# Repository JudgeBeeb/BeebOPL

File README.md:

# BeebOPL
## An FM synthesiser for the BBC Microcomputer based on the YM3812

This is an FM Synthesiser Sound Card for the BBC Microcomputer. It is based on the YM3812 chip as used in the Ad Lib Sound Card and the original Soundblaster. 

It connects to the 1MHz Bus and is programmed by reference to two addresses in the BBC memory map. These are `YMADDR` (&FC04) and `YMDATA` (&FC04).

For some samples of what BeebOPL can do have a look at this [playlist on SoundCloud] (https://soundcloud.com/user-469563483/sets/beebopl-1)

The `DROPLAY` utility will play _DOSBox Raw OPL_ (DRO) version 2.0 files natively. These files can be generated by playing any OPL file in DOSBox (version 0.74). Visit http://www.dosbox.com for details.

The syntax for the compiled executable is `*DROPLAY <fsp>`. The code is compiled to load in the page above `PAGE`. It loads as much as it can of the DRO file from the page immediately above the program up to the page below `HIMEM`. If the entire file fits into memory, it is simply played from memory. Otherwise, further data is streamed from the disc using `OSGBPB` in the form of a circular buffer. 

All disc reads take place in the foreground. The music player itself is an interrupt driven background task. Interrupts are generated by the YM3812 timer. This avoids using the User VIA timer as this seems to interfere with certain solid state filing system.

**_Issues and to do_**

- [x] ~~System crashes following use of the `ESCAPE` key.~~

- [x] ~~Check for the presence of a BeebOPL card before attempting to play a file and issue error.~~

- [x] ~~Include error messages for card not found, not a valid DRO file, unsupported DRO version, wrong card version and compressed file not supported.~~ 

- [ ] The YM3812 flush routine doesn't seem to work all the time. Subsequent tunes can be a little corrupted if they are played without a preceding hard break.

- [ ] Due to an inherent problem with OSGBPB, the filing system cannot keep up with the demands of particularly large/complex DRO files. The player effectively '_laps_' the circular buffer and starts repeating the same segment of the file.

- [x] ~~Check if the entire DRO file will fit in memory and, if so, load it with `OSFILE` rather than `OSGBPB` to speed up loading times.~~

- [ ] Address continuing minor timing issues. (These seem to be getting worse!) ~~DRO timing data is based on milliseconds. The YM3812 timer updates every 80 microseconds and therefore cannot measure precisely one millisecond.~~ 

- [x] ~~Check to see if player has overtaken buffer and issue error.~~

- [x] ~~Find a neat way to deal with buffering messages in Juke Box.~~

- [x] ~~The registers are flushed too soon. Need to leave time for the last note to fade.~~

- [x] ~~Generally tidy up code; in particular using curly braces and local variables.~~

- [x] ~~Juke Box inexplicably occasionally reports "BeebOPL card not found".~~

- [x] ~~The 3.5mm jack socket is about 1mm too far over to the left and therefore does not fit well. This needs to be corrected if another run of boards is done.~~

- [] There is an error on the PCB silk screen at the 'floppy' style power connector. 5v and 12v are reversed.

Further down the line, I would like to see if the use of [Exomiser] (http://hem.bredband.net/magli143/exo/) could be incorporated.

I would also like to see if I could include **kieranhj**'s direct track loading routines using `OSWORD` (which he uses in his amazing [Mode 7 Video] (https://github.com/kieranhj/mode7-video) project). This may resolves the problems associated with `OSGBPB`.

It would also be useful if there could be some kind of (software) master volume control.

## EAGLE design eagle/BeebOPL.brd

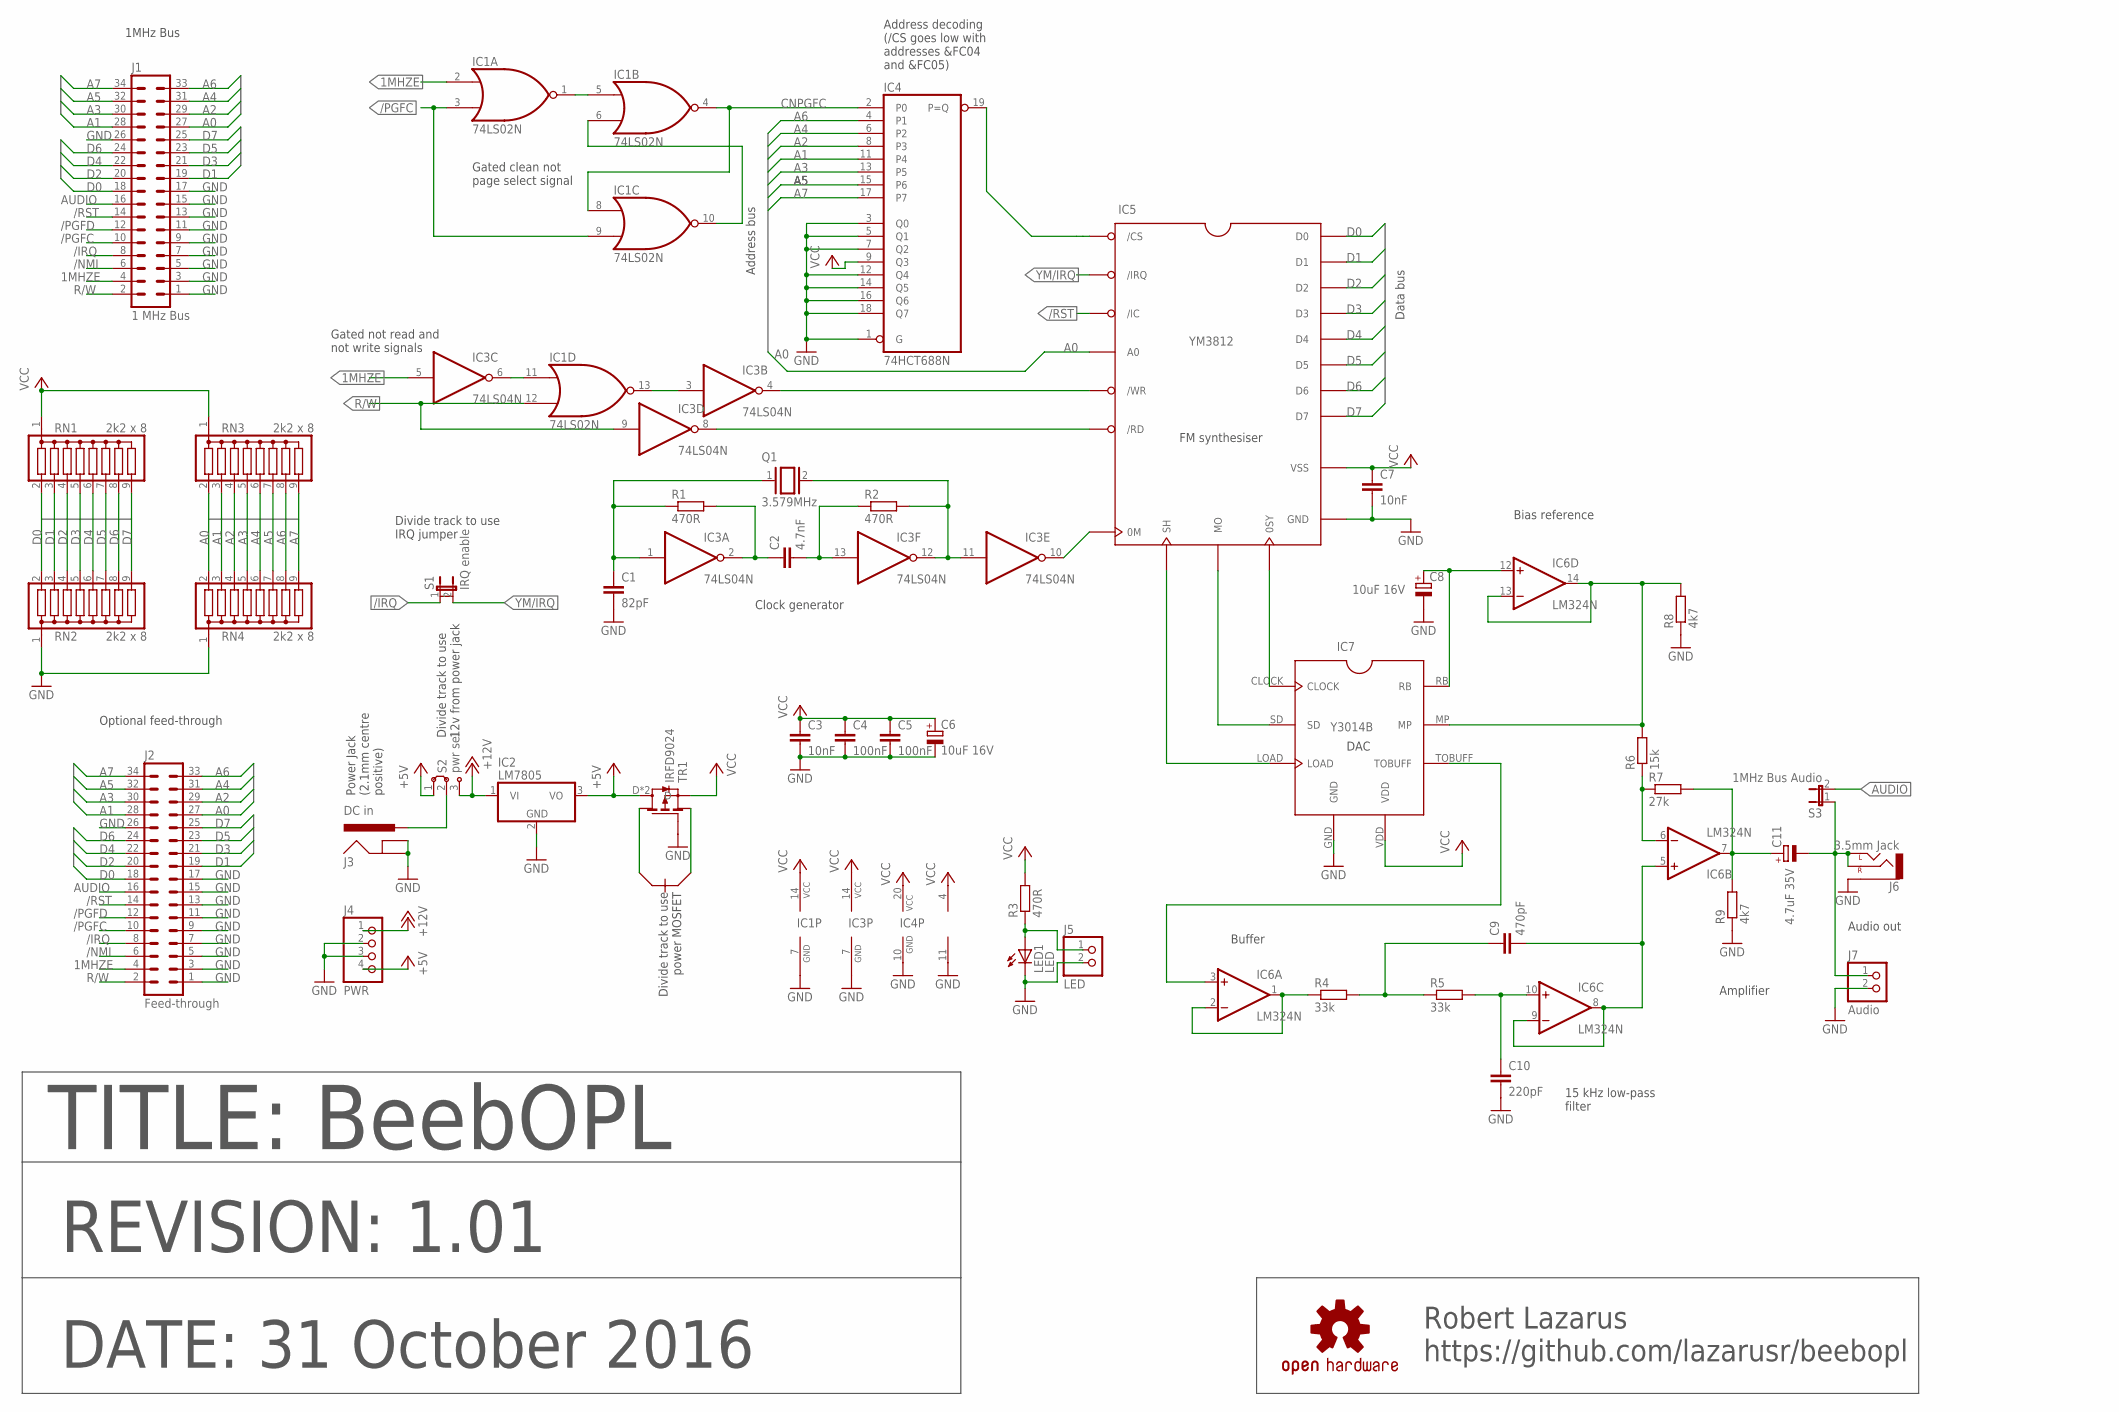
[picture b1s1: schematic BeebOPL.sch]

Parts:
C1: 82pF; C050-024X044
C2: 4.7nF; C050-024X044
C3, C7: 10nF; C050-024X044
C4, C5: 100nF; C050-024X044
C6, C8: 10uF 16V; E2,5-5
C9: 470pF; C050-024X044
C10: 220pF; C050-024X044
C11: 4.7uF 35V; E2,5-5
IC1: 74LS02N; DIL14
IC2: LM7805; TO220V
IC3: 74LS04N; DIL14
IC4: 74HCT688N; DIL20
IC5: YM3812
IC6: LM324N; DIL14
IC7: Y3014B; YM3014B
J1: 1 MHz Bus; ML34
J2: Feed-through; ML34
J3: DC in; POWER_JACK_SLOT
J4: PWR; 1X04
J5: LED; 1X02
J6: 3.5mm Jack; AUDIO-JACK
J7: Audio; 1X02
LED1: LED; LED5MM
LOGO1: OSHW-LOGO-BOTTOML; OSHW-LOGO-L
Q1: 3.579MHz; QS
R1, R2, R3: 470R; 0207/10
R4, R5: 33k; 0207/10
R6: 15k; 0207/10
R7: 27k; 0207/10
R8, R9: 4k7; 0207/10
RN1, RN2, RN3, RN4: 2k2 x 8; SIL9
S1: IRQ enable; 1X02
S2: pwr sel; S_3WAY_OR
S3: 1MHz Bus Audio; 1X02
TR1: IRFD9024; FET-DIL-OPTN

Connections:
1MHZE: IC1.2 (I0), IC3.5 (I), J1.4, J2.4
+5V: IC2.3 (VO), J4.4, S2.1, TR1.D, TR1.D1 (D)
+12V: IC2.1 (VI), J4.1, S2.3
/IRQ: J1.8, J2.8, S1.1
/NMI: J1.6, J2.6
/PGFC: IC1.3 (I1), IC1.9 (I1), J1.10, J2.10
/PGFD: J1.12, J2.12
/RST: IC5./IC, J1.14, J2.14
A0: IC5.A0, J1.27, J2.27, RN3.2, RN4.2
A1: IC4.11 (P4), J1.28, J2.28, RN3.3, RN4.3
A2: IC4.8 (P3), J1.29, J2.29, RN3.4, RN4.4
A3: IC4.13 (P5), J1.30, J2.30, RN3.5, RN4.5
A4: IC4.6 (P2), J1.31, J2.31, RN3.6, RN4.6
A5: IC4.15 (P6), J1.32, J2.32, RN3.7, RN4.7
A6: IC4.4 (P1), J1.33, J2.33, RN3.8, RN4.8
A7: IC4.17 (P7), J1.34, J2.34, RN3.9, RN4.9
AUDIO: J1.16, J2.16, S3.2
AUDIO_OUT: C11.-, J6.RING (RIGHT), J6.TIP (LEFT), J7.1, S3.1
CNPGFC: IC1.4 (O), IC1.8 (I0), IC4.2 (P0)
D0: IC5.D0, J1.18, J2.18, RN1.2, RN2.2
D1: IC5.D1, J1.19, J2.19, RN1.3, RN2.3
D2: IC5.D2, J1.20, J2.20, RN1.4, RN2.4
D3: IC5.D3, J1.21, J2.21, RN1.5, RN2.5
D4: IC5.D4, J1.22, J2.22, RN1.6, RN2.6
D5: IC5.D5, J1.23, J2.23, RN1.7, RN2.7
D6: IC5.D6, J1.24, J2.24, RN1.8, RN2.8
D7: IC5.D7, J1.25, J2.25, RN1.9, RN2.9
DC: J3.PWR, S2.2
GND: C1.2, C3.2, C4.2, C5.2, C6.-, C7.2, C8.-, C10.2, IC1.7 (GND), IC2.2 (GND), IC3.7 (GND), IC4.1 (G), IC4.3 (Q0), IC4.5 (Q1), IC4.7 (Q2), IC4.10 (GND), IC4.12 (Q4), IC4.14 (Q5), IC4.16 (Q6), IC4.18 (Q7), IC5.GND, IC6.11 (V-), IC7.GND, J1.1, J1.3, J1.5, J1.7, J1.9, J1.11, J1.13, J1.15, J1.17, J1.26, J2.1, J2.3, J2.5, J2.7, J2.9, J2.11, J2.13, J2.15, J2.17, J2.26, J3.GND@1 (GNDBREAK), J3.GND@2 (GND), J4.2, J4.3, J5.2, J6.SLEEVE, J7.2, LED1.K (C), R8.1, R9.1, RN2.1, RN4.1, TR1.G
unnamed: C2.1, IC3.2 (O), R1.2
unnamed: IC1.13 (O), IC3.3 (I)
unnamed: IC1.11 (I0), IC3.6 (O)
unnamed: C2.2, IC3.13 (I), R2.1
unnamed: IC5.SH, IC7.LOAD
unnamed: IC5.MO, IC7.SD
unnamed: IC5.0SY, IC7.CLOCK
unnamed: C1.1, IC3.1 (I), Q1.1, R1.1
unnamed: IC1.1 (O), IC1.5 (I0)
unnamed: C8.+, IC6.12 (+IN), IC7.RB
unnamed: IC1.6 (I1), IC1.10 (O)
unnamed: IC6.13 (-IN), IC6.14 (OUT), IC7.MP, R6.2, R8.2
unnamed: IC3.8 (O), IC5./RD
unnamed: IC6.6 (-IN), R6.1, R7.1
unnamed: C11.+, IC6.7 (OUT), R7.2, R9.2
unnamed: IC6.3 (+IN), IC7.TOBUFF
unnamed: IC6.1 (OUT), IC6.2 (-IN), R4.1
unnamed: C9.1, R4.2, R5.1
unnamed: C10.1, IC6.10 (+IN), R5.2
unnamed: C9.2, IC6.5 (+IN), IC6.8 (OUT), IC6.9 (-IN)
unnamed: IC4.19 (P=Q), IC5./CS
unnamed: IC3.4 (O), IC5./WR
unnamed: J5.1, LED1.A, R3.1
unnamed: IC3.10 (O), IC5.0M
unnamed: IC3.11 (I), IC3.12 (O), Q1.2, R2.2
R/W: IC1.12 (I1), IC3.9 (I), J1.2, J2.2
VCC: C3.1, C4.1, C5.1, C6.+, C7.1, IC1.14 (VCC), IC3.14 (VCC), IC4.9 (Q3), IC4.20 (VCC), IC5.VSS, IC6.4 (V+), IC7.VDD, R3.2, RN1.1, RN3.1, TR1.S
YM/IRQ: IC5./IRQ, S1.2

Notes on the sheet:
Address decoding (/CS goes low with addresses &FC04 and &FC05)
Power Jack (2.1mm centre positive)
1MHz Bus
Optional feed-through
Data bus
Address bus
Gated clean not page select signal
Gated not read and not write signals
Clock generator
FM synthesiser
DAC
Bias reference
Audio out
Amplifier
Buffer
15 kHz low-pass filter
TITLE: BeebOPL
REVISION: 1.01
DATE: 31 October 2016
Divide track to use 12v from power jack
Divide track to use power MOSFET
Divide track to use IRQ jumper
Robert Lazarus https://github.com/lazarusr/beebopl

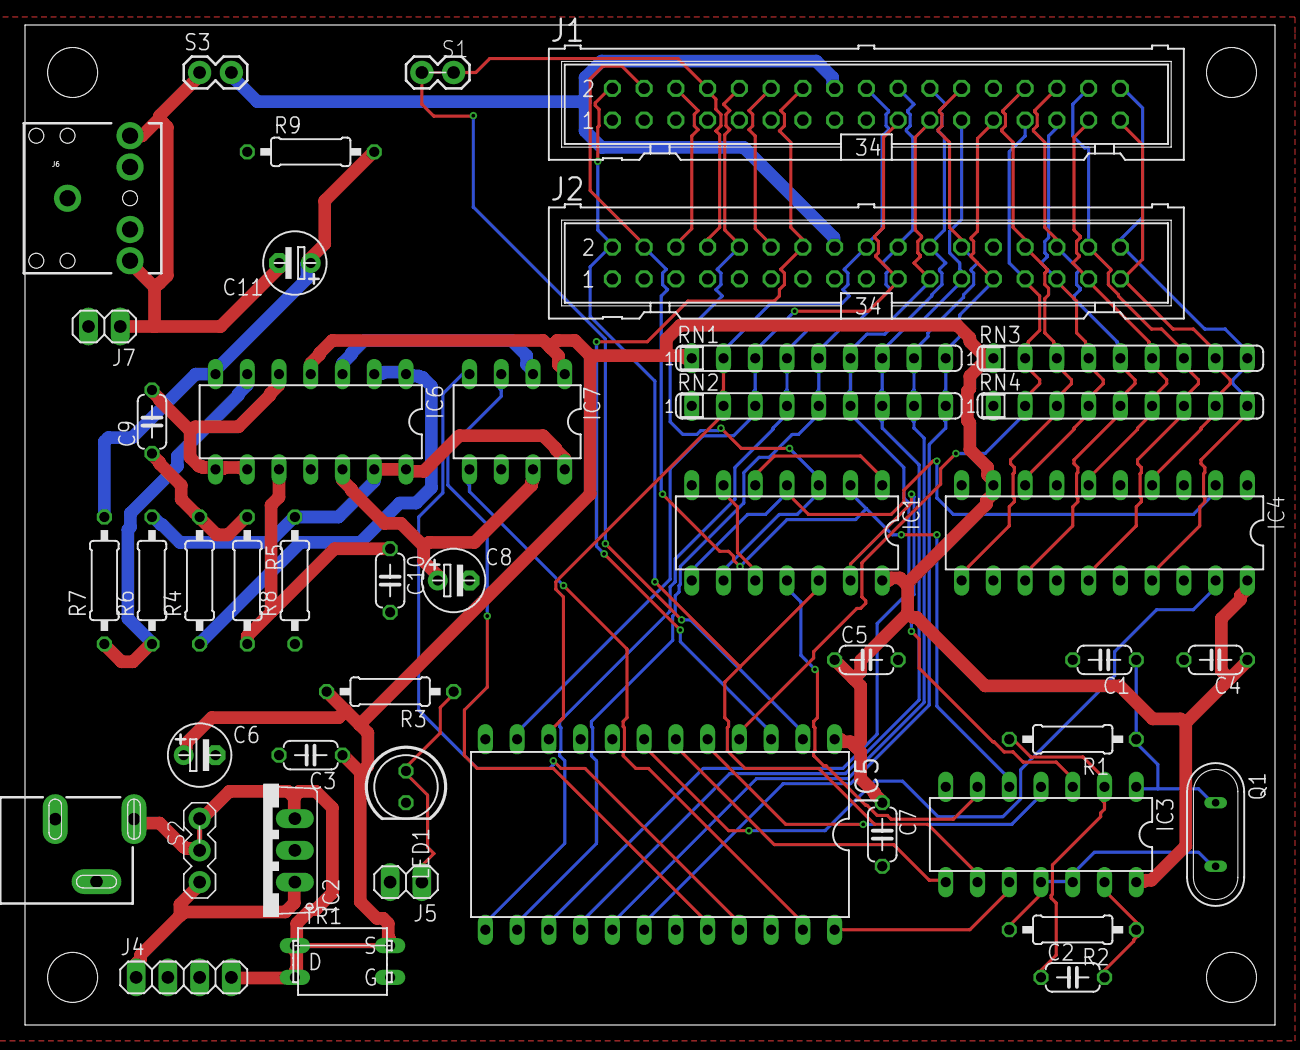
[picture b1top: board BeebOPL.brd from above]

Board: 2 copper layers, 100.0 x 80.0 mm, 45 parts (0 on the bottom side), 57 nets.

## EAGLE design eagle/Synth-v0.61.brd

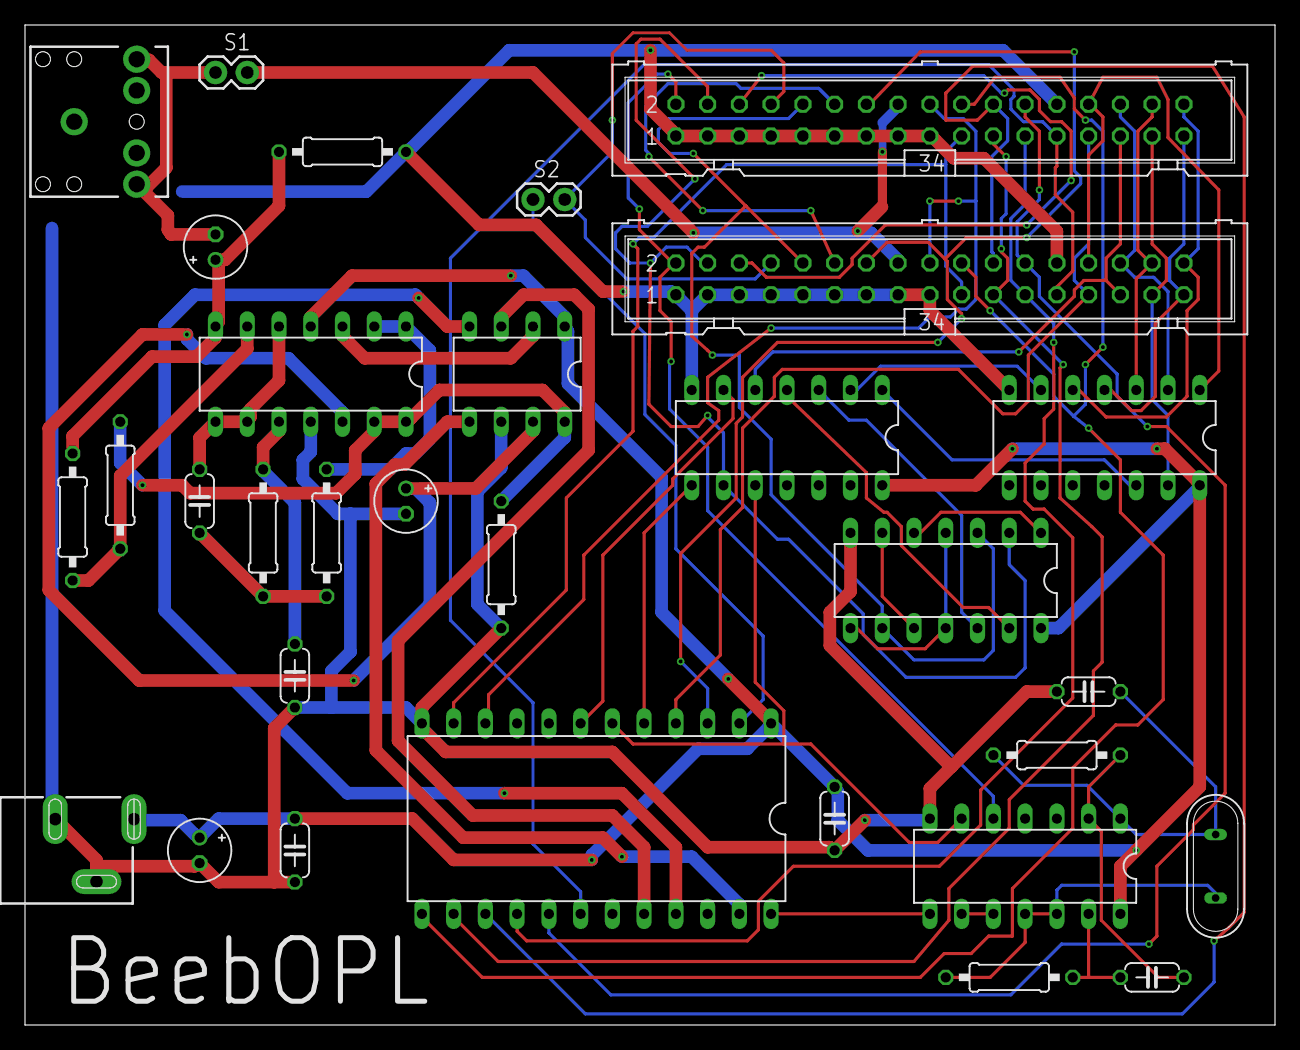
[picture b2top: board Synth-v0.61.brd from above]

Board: 2 copper layers, 100.0 x 80.0 mm, 31 parts (0 on the bottom side), 56 nets.

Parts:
C1: 4.7uF 35V; E2-5
C2: 470pF; C050-024X044
C3, C6: 10uF 16V; E2-5
C4: 220pF; C050-024X044
C5: 82pF; C050-024X044
C7, C8: 10nF; C050-024X044
C9: 4.7nF; C050-024X044
IC1: LM324N; DIL14
IC2: YM3014B
IC3: 74LS00N; DIL14
IC4: 74LS27N; DIL14
IC5: 74LS02N; DIL14
IC6: YM3812
IC7: 74LS04N; DIL14
J1: 1 MHz Bus; ML34
J2: Feed-through; ML34
J3: 3.5mm Jack; AUDIO-JACK
J4: 5V DC; POWER_JACK_SLOT
R1, R6: 4k7; 0207/10
R2: 27k; 0207/10
R3: 15k; 0207/10
R4, R5: 33k; 0207/10
R7, R8: 470R; 0207/10
S1: 1MHz Bus Audio; 1X02
S2: IRQ; 1X02
XTAL1: 3.579MHz; QS

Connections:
1MHZE: IC3.9, IC5.2, J1.4, J2.4
/IRQ: J1.8, J2.8, S2.2
/NMI: J1.6, J2.6
/PGFC: IC5.3, IC5.9, J1.10, J2.10
/PGFD: J1.12, J2.12
/RD: IC3.10, IC6./RD, IC7.6
/RST: IC6./IC, J1.14, J2.14
A0: IC6.A0, J1.27, J2.27
A1: IC4.1, J1.28, J2.28
A2: IC3.5, J1.29, J2.29
A3: IC4.2, J1.30, J2.30
A4: IC4.13, J1.31, J2.31
A5: IC4.3, J1.32, J2.32
A6: IC4.4, J1.33, J2.33
A7: IC4.5, J1.34, J2.34
AUDIO: J1.16, J2.16, S1.2
CNPGFC: IC5.4, IC5.8, IC5.11
D0: IC6.D0, J1.18, J2.18
D1: IC6.D1, J1.19, J2.19
D2: IC6.D2, J1.20, J2.20
D3: IC6.D3, J1.21, J2.21
D4: IC6.D4, J1.22, J2.22
D5: IC6.D5, J1.23, J2.23
D6: IC6.D6, J1.24, J2.24
D7: IC6.D7, J1.25, J2.25
GND: C3.-, C4.2, C5.2, C6.-, C7.2, C8.2, IC1.11, IC2.GND, IC3.7, IC4.7, IC5.7, IC6.GND, IC7.7, J1.1, J1.3, J1.5, J1.7, J1.9, J1.11, J1.13, J1.15, J1.17, J1.26, J2.1, J2.3, J2.5, J2.7, J2.9, J2.11, J2.13, J2.15, J2.17, J2.26, J3.SLEEVE, J4.GND@1, J4.GND@2, R1.1, R6.1
unnamed: C9.1, IC7.2, R7.2
unnamed: IC3.1, IC4.12
unnamed: IC3.2, IC4.6
unnamed: IC7.11, IC7.12, R8.2, XTAL1.2
unnamed: C9.2, IC7.13, R8.1
unnamed: IC2.LOAD, IC6.SH
unnamed: IC2.SD, IC6.MO
unnamed: IC2.CLOCK, IC6.0SY
unnamed: C5.1, IC7.1, R7.1, XTAL1.1
unnamed: IC5.1, IC5.5
unnamed: C3.+, IC1.12, IC2.RB
unnamed: IC5.6, IC5.10
unnamed: IC1.13, IC1.14, IC2.MP, R3.2, R6.2
unnamed: IC3.3, IC5.12
unnamed: IC1.6, R2.1, R3.1
unnamed: C1.+, IC1.7, R1.2, R2.2
unnamed: C1.-, J3.RING, J3.TIP, S1.1
unnamed: IC1.3, IC2.TOBUFF
unnamed: IC1.1, IC1.2, R5.1
unnamed: C2.1, R4.1, R5.2
unnamed: C4.1, IC1.10, R4.2
unnamed: C2.2, IC1.5, IC1.8, IC1.9
unnamed: IC3.4, IC5.13
unnamed: IC3.8, IC6./WR
unnamed: IC6.0M, IC7.8
unnamed: IC7.9, IC7.10
unnamed: IC3.6, IC6./CS
R/W: IC7.5, J1.2, J2.2
VCC: C6.+, C7.1, C8.1, IC1.4, IC2.VDD, IC3.14, IC4.14, IC5.14, IC6.VSS, IC7.14, J4.PWR
YM/IRQ: IC6./IRQ, S2.1

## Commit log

2016-08-30 First working DRO player
    Has lots of code commented out at the moment. To do: (i) identify why this works with the 6522 timer, but not with the YM3812 timer; (ii) enable code to allow app to stream DRO data from disc.
2016-08-30 Rename droplay to droplet.asm
2016-08-30 Rename droplet.asm to droplay.6502
2016-08-30 Rename droplay.6502 to droplay.asm
2016-08-30 Rename droplay.asm to droplay.s
2016-08-30 Rename droplay.s to droplay.s.6502
2016-08-30 Rename droplay.s.6502 to droplay.6502
2016-08-30 Create dummy
2016-08-30 William Tell Overture
2016-09-25 --alllow-empty
2016-09-25 Revert "Delete eagle.epf"
    This reverts commit e274904fad405036d6351e49f96f02e79d0e902d.
2016-09-25 Revert "Update README.md"
    This reverts commit cd072b5b50124194fb9ae64a69794f0bf7d27940.
2016-09-25 Added more music files
2016-09-25 Added new tune
2016-09-26 Added new error codes
2016-09-26 Updated .gitignore to get rid of unnecessary Eagle files
2016-09-26 Removed Gerber files
2016-09-26 Renamed Eagle files
2016-09-26 Corrected spelling error in comments
2016-09-26 Escape function working
2016-09-26 Added routine to check for the presence of a BeebOPL card
2016-09-27 Replaced 74LS27 with 74HCT688
2016-09-27 Added mounting holes
2016-09-27 Removed 74LS00
2016-09-27 Added resistor networks
2016-09-27 Added optional power regualtor
2016-09-27 Added power options
2016-09-27 Set IRQ as connected by default
2016-09-29 Tidied-up schematic
2016-09-29 Further refined schematic
2016-09-29 Perfecting schematic
2016-09-30 More sophisticated power section
2016-09-30 Assigned net classes
2016-09-30 Initial board layout
2016-09-30 Routing signals
2016-09-30 Further routing
2016-10-01 Manual routing not complete
2016-10-01 Finished routing
2016-10-01 Added silkscreen
2016-10-02 Final board sent to fab
2016-10-02 Modified .gitignore
2016-10-02 Added pdf schematic to docs
2016-10-02 Removed footer from schematic
2016-10-02 Minor presentational changes
2016-10-02 Corrected bug in card checking routine
2016-10-02 Created fake music files for debugging
2016-10-02 Error checking for wrong file types
2016-10-02 First version of Jukebox
2016-10-03 Added image of PCB
2016-10-03 Minor changes to silkscreen
2016-10-04 Added better images of PCB
2016-10-05 Ignoring opl3 folder
2016-10-08 Updated PCB images with more realistic colours
2016-10-08 Updated .gitignore
2016-10-08 Minor cosmetic change
2016-10-08 Added -TEST switch
2016-10-08 Added all the tunes from the original Ad Lib Juke Box proram
2016-10-08 Substantial changes to Juke Box with its own bespoke jukplay app
2016-10-09 Significant update to Juke Box
2016-10-09 Ported relevant improvements in Juke Box across to Droplay
2016-10-12 Modified README.md
2016-10-12 Minor presentational improvements
2016-10-12 Added more details of available zero page memory
2016-10-12 Added option to use zero page as workspace
2016-10-12 Changed old_event_status flags to mirror MOS event numbers
2016-10-15 Added User Guide
2016-10-15 Added library of useful routines (not written by me)
2016-10-15 Minor changes to Juke Box
2016-10-15 Tidied up music directory
2016-10-15 Major rewrite of the DROPLAY code
2016-10-16 Optimised code
2016-10-17 Removed debugging data display from release version
2016-10-17 Added new music
2016-10-18 Minor changes
2016-10-18 Added more music
2016-10-18 Corrected an error where the final notes didn't sustain
2016-10-18 Ported improvements to DROPLAY code across to JUKE BOX
2016-10-19 Added more tunes
2016-10-21 Improved code for countdown timer
2016-10-30 Added variants of software to run with PAGE set to a higher value
2016-10-30 Corrected minor error
2016-10-31 Corrected error with position of 3.5mm socket
2016-11-02 Juke Box will now display buffering message for longer files
2016-11-14 Clarified the purpose of the high page variant builds
2016-12-06 Added bonus disc and music
2016-12-06 Updated User Guide to Issue no 1.1
2016-12-19 Added Christmas tunes
2017-01-29 Corrected memory bug in latest Juke Box version
2017-03-18 Noted serious error on PCB screen.
2017-05-13 Refreshing repo
2017-05-13 Updated User Guide
2017-05-13 Corrected memory error
2017-05-15 New music added

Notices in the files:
parts and their libraries:
SparkFun-Connectors: Licensing: Creative Commons ShareAlike 4.0 International - https://creativecommons.org/licenses/by-sa/4.0
